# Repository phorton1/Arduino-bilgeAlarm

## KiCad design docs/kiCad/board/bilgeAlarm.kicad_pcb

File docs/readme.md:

# bilgeAlarm - Home

**Home** --
**[History](history.md)** --
**[Previous](previous.md)** --
**[Design](design.md)** --
**[Hardware](hardware.md)** --
**[Software](software.md)** --
**[UI](user_interface.md)**

The **bilgeAlarm** is the most important device I have created for my boat,
[**Rhapsody**](http://www.phorton.com/html/Rhapsody.html). It is a device
for monitoring the bilge pump(s) on the boat, sounding a **loud alarm**
if the bilge pump runs too long, or too often.  It is the result of
[almost sinking Rhapsody](history.md) one time when the bilge pump ran,
but could not be heard, until it **burnt out** and the boat took on 1000's of
gallons of water, resulting in **serious damage** and a huge amount of repairs ...
and time and money ... to fix the problems caused by the flooding.

This bilgeAlarm uses an **ESP32** and is based on an
[earlier](previous.md) **Arduino** project, now lost to antiquity,
that I called the *bilgePumpSwitch*.
It uses the [**myIOT**](https://github.com/phorton1/Arduino-libraries-myIOT) library
for parametrization and to allow me to control and monitor it remotely.
It has an **SD Card** to keep prodigious amounts of history about the bilge pump,
and uses **WS3812b** leds for visual indicators, and a **very loud car alarm**,
that can be heard above the motor running and the sound of the boat when she is
underway and crashing through waves to ensure that **I know** if there is a problem
with water entering the boat.

On these pages I will document the [**design**](design.md) of the bilgeAlarm along with
how I created the [**hardware**](hardware.md) and [**software**](software.md) for
the device and provide a rudimentary [**user guide**](user_interface.md) for using it.

All of the **source code, schematics,** and **files** needed to create this
device can be found within the **docs** folder:

- **kicad** - the kicad *schematics* and *pcb* layouts and the **flatcam** project and gcode files to mill and create the PCBs
- **fusion** - the fusion 360 design files for the plastic box
- **stl** - the STL files that I used for 3D printing the box
- **prusa** - the Prusa slicer files and resultant gcode I used to print the box

## Required Libraries

To build this project, you will need to install the
[**myIOT library**](https://github.com/phorton1/Arduino-libraries-myIOT)
and it's dependencies.  Please see that project for details about **installation**
and building.

In addition, this project makes use of two standard libraries that can
be installed to the **Arduino IDE** using the *Tools - Library Manager*:

- Adafruit_neoPixels
- LiquidCrystal_I2C

## License

This program is free software: you can redistribute it and/or modify
it under the terms of the GNU General Public License Version 3 as published by
the Free Software Foundation.

This program is distributed in the hope that it will be useful,
but WITHOUT ANY WARRANTY; without even the implied warranty of
MERCHANTABILITY or FITNESS FOR A PARTICULAR PURPOSE.  See the
GNU General Public License for more details.

Please see [LICENSE.TXT](https://github.com/phorton1/Arduino-libraries-myIOT/blob/master/LICENSE.TXT) for more information.

Next: The **[story](history.md)** behind the bilgeAlarm ...

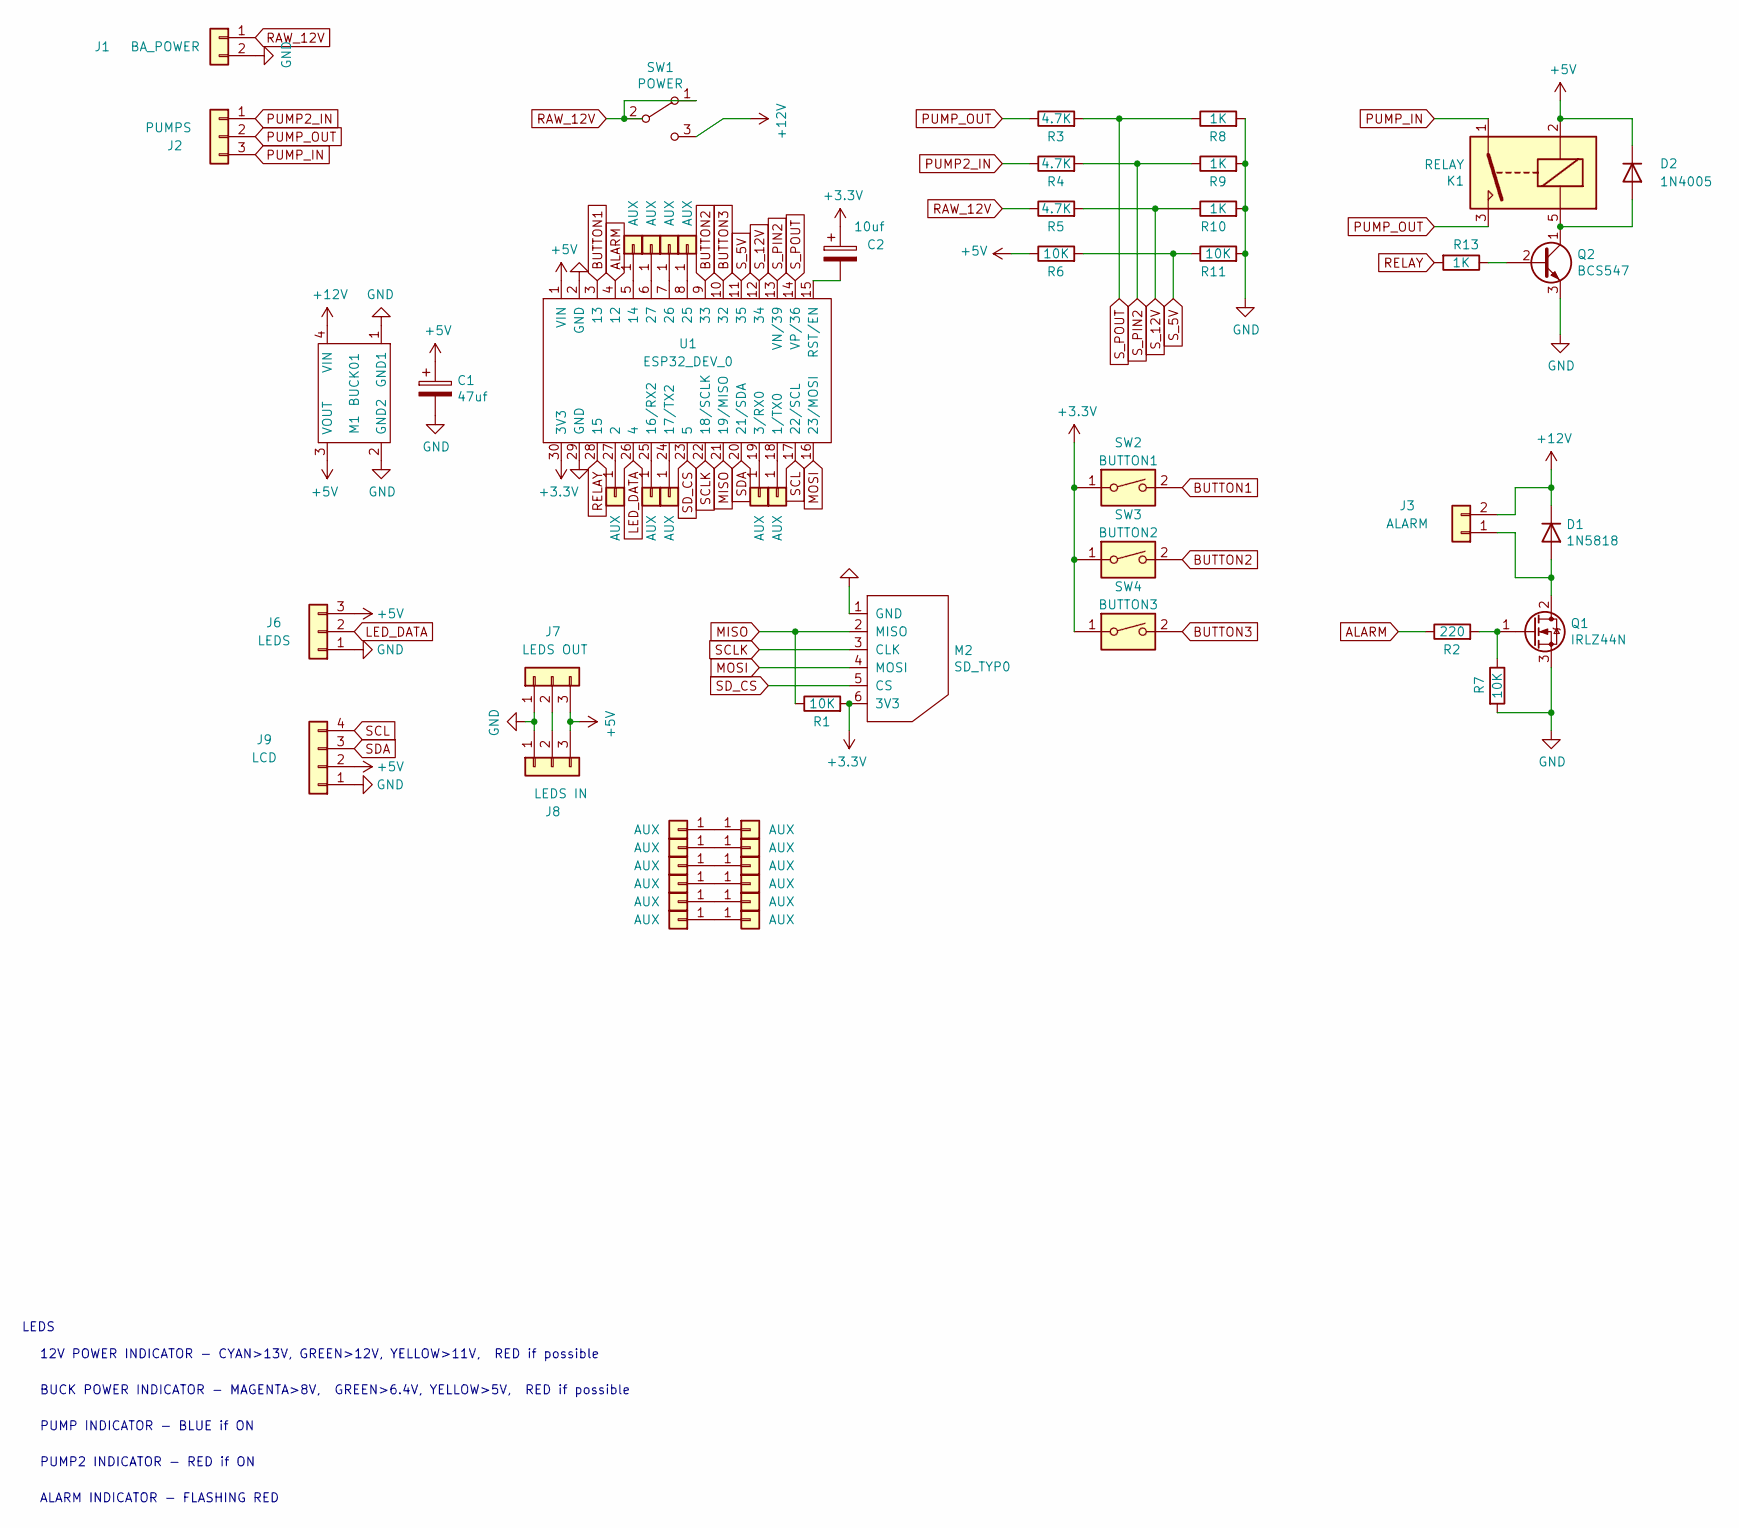
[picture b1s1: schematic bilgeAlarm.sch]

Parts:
C1: 47uf; CP_my100uf
C2: 10uf; CP_my10uf
D1: 1N5818; myDiodeSchotsky
D2: 1N4005; myDiodeSchotsky
J1: BA_POWER; myTerminalBlock_5.08x02
J2: PUMPS; myTerminalBlock_5.08x03
J3: ALARM; myTerminalBlock_5.08x02
J6: LEDS; myPinSocket_1x03
J7: LEDS OUT; myPinSocket_1x03
J8: LEDS IN; myPinSocket_1x03
J9: LCD; myPinSocket_1x04
J21, J22, J23, J24, J25, J26, J27, J28, J29, J30, J31, J32, J33, J34, J35, J36, J37, J38, J39, J40, J41: AUX; my1pin
K1: RELAY; myRelay
M1: BUCK01; myMini360BuckConverter
M2: SD_TYP0; SDCardReader
Q1: IRLZ44N; myTO-220-3
Q2: BCS547; my3pin
R1, R6, R7, R11: 10K; myResistor
R2: 220; myResistor
R3, R4, R5: 4.7K; myResistor
R8, R9, R10, R13: 1K; myResistor
SW1: POWER; mySwitchToggleSPDT
SW2: BUTTON1; myButton
SW3: BUTTON2; myButton
SW4: BUTTON3; myButton
U1: ESP32_DEV_0; myESP32DEV0

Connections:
+3V3: C2.1, M2.6 (3V3), R1.2, SW2.1, SW3.1, SW4.1, U1.30 (3V3)
+5V: C1.1, D2.1 (K), J6.3, J7.3, J8.3, J9.2, K1.2, M1.3 (VOUT), R6.1, U1.1 (VIN)
+12V: D1.1 (K), J3.2, M1.4 (VIN), SW1.3 (C)
ALARM: R2.1, U1.4 (12)
BUTTON1: SW2.2, U1.3 (13)
BUTTON2: SW3.2, U1.9 (33)
BUTTON3: SW4.2, U1.10 (32)
GND: C1.2, J1.2, J6.1, J7.1, J8.1, J9.1, M1.1 (GND1), M1.2 (GND2), M2.1 (GND), Q1.3 (S), Q2.3 (E), R7.2, R8.2, R9.2, R10.2, R11.2, U1.2 (GND), U1.29 (GND)
LED_DATA: J6.2, U1.26 (4)
MISO: M2.2 (MISO), R1.1, U1.21 (19/MISO)
MOSI: M2.4 (MOSI), U1.16 (23/MOSI)
unnamed: C2.2, U1.15 (RST/EN)
unnamed: D1.2 (A), J3.1, Q1.2 (D)
unnamed: D2.2 (A), K1.5, Q2.1 (C)
unnamed: J7.2, J8.2
unnamed: J21.1, U1.27 (2)
unnamed: J22.1, U1.25 (16/RX2)
unnamed: J23.1, U1.24 (17/TX2)
unnamed: J24.1, U1.5 (14)
unnamed: J25.1, U1.7 (26)
unnamed: J26.1, U1.8 (25)
unnamed: J27.1, U1.19 (3/RX0)
unnamed: J28.1, U1.18 (1/TX0)
unnamed: J29.1, U1.6 (27)
unnamed: J30.1, J36.1
unnamed: J31.1, J37.1
unnamed: J32.1, J38.1
unnamed: J33.1, J39.1
unnamed: J34.1, J40.1
unnamed: J35.1, J41.1
unnamed: Q1.1 (G), R2.2, R7.1
unnamed: Q2.2 (B), R13.1
PUMP2_IN: J2.1, R4.1
PUMP_IN: J2.3, K1.1
PUMP_OUT: J2.2, K1.3, R3.1
RAW_12V: J1.1, R5.1, SW1.1 (A), SW1.2 (B)
RELAY: R13.2, U1.28 (15)
SCL: J9.4, U1.17 (22/SCL)
SCLK: M2.3 (CLK), U1.22 (18/SCLK)
SDA: J9.3, U1.20 (21/SDA)
SD_CS: M2.5 (CS), U1.23 (5)
S_5V: R6.2, R11.1, U1.11 (35)
S_12V: R5.2, R10.1, U1.12 (34)
S_PIN2: R4.2, R9.1, U1.13 (VN/39)
S_POUT: R3.2, R8.1, U1.14 (VP/36)

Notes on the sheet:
LEDS
12V POWER INDICATOR - CYAN>13V, GREEN>12V, YELLOW>11V, RED if possible
BUCK POWER INDICATOR - MAGENTA>8V, GREEN>6.4V, YELLOW>5V, RED if possible
PUMP INDICATOR - BLUE if ON
PUMP2 INDICATOR - RED if ON
ALARM INDICATOR - FLASHING RED

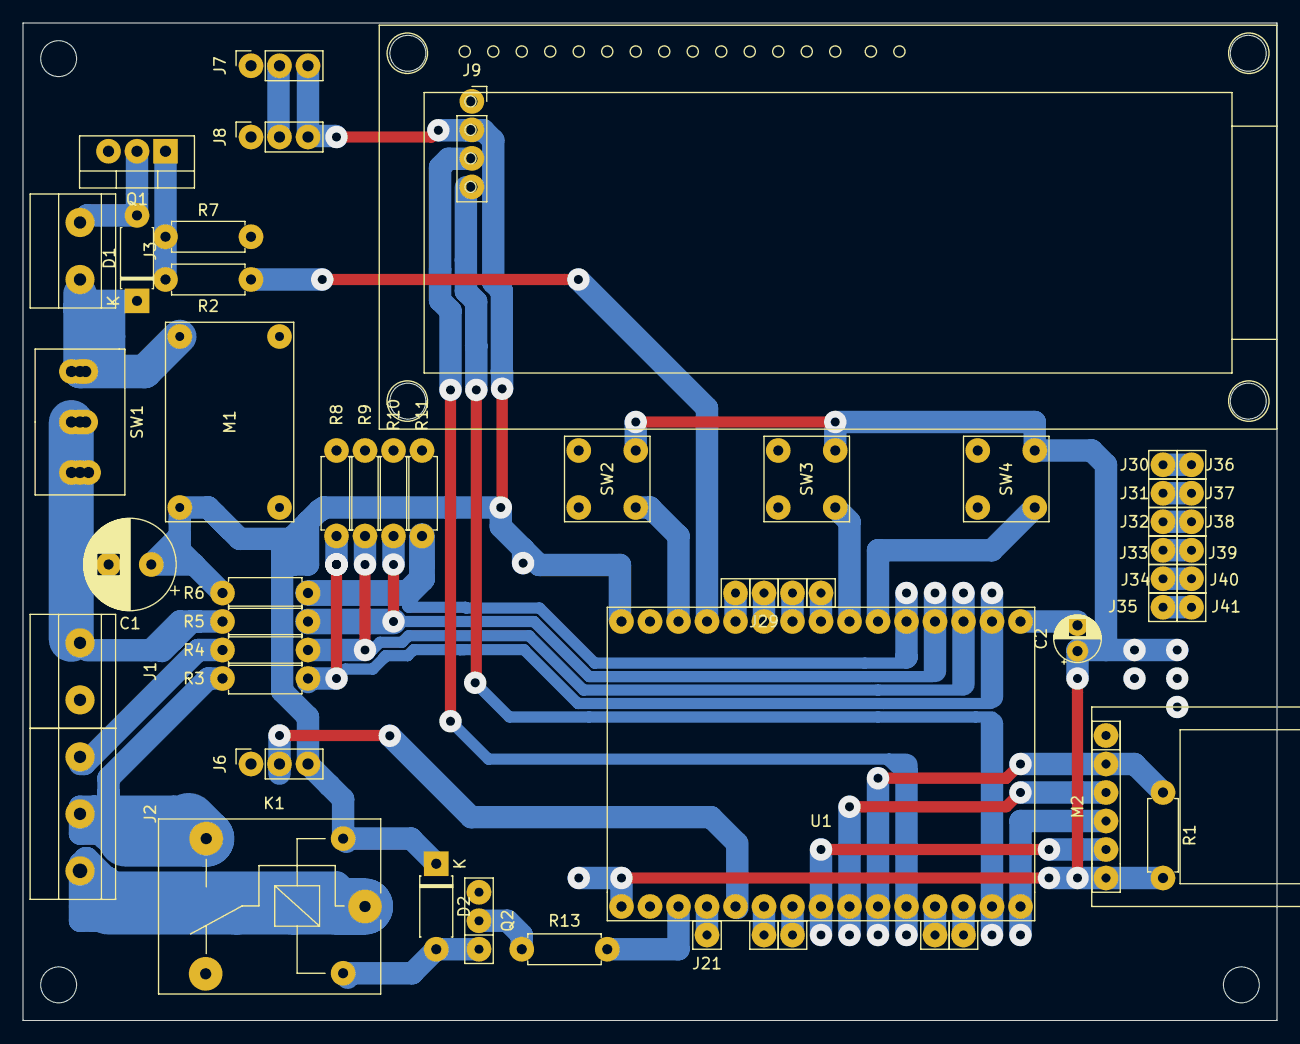
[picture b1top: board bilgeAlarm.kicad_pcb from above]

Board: 2 copper layers, 111.8 x 88.9 mm, 54 parts (0 on the bottom side), 45 nets.

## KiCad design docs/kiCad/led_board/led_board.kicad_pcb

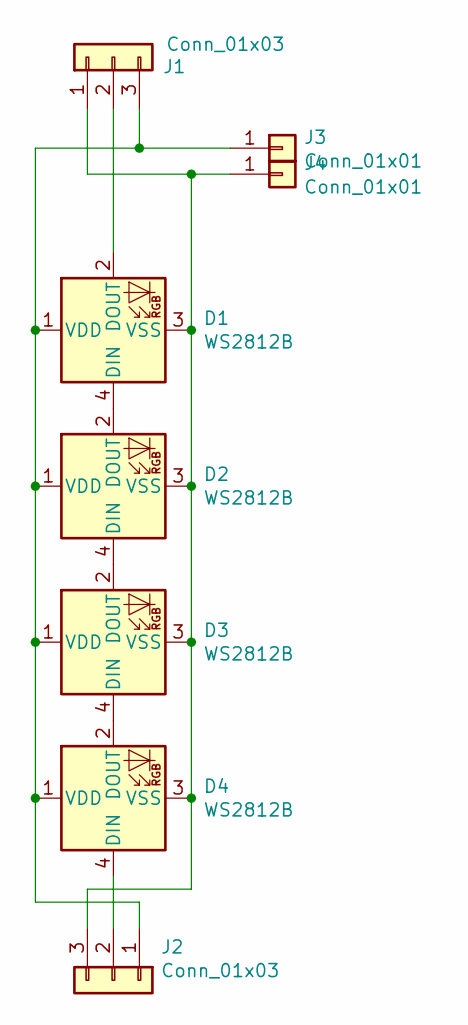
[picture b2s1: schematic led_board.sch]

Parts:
D1, D2, D3, D4: WS2812B; myWS2812
J1, J2: Conn_01x03; my3pin
J3, J4: Conn_01x01; my1pin

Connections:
unnamed: D1.1 (VDD), D2.1 (VDD), D3.1 (VDD), D4.1 (VDD), J1.3, J2.1, J3.1
unnamed: D1.2 (DOUT), J1.2
unnamed: D1.3 (VSS), D2.3 (VSS), D3.3 (VSS), D4.3 (VSS), J1.1, J2.3, J4.1
unnamed: D1.4 (DIN), D2.2 (DOUT)
unnamed: D2.4 (DIN), D3.2 (DOUT)
unnamed: D3.4 (DIN), D4.2 (DOUT)
unnamed: D4.4 (DIN), J2.2

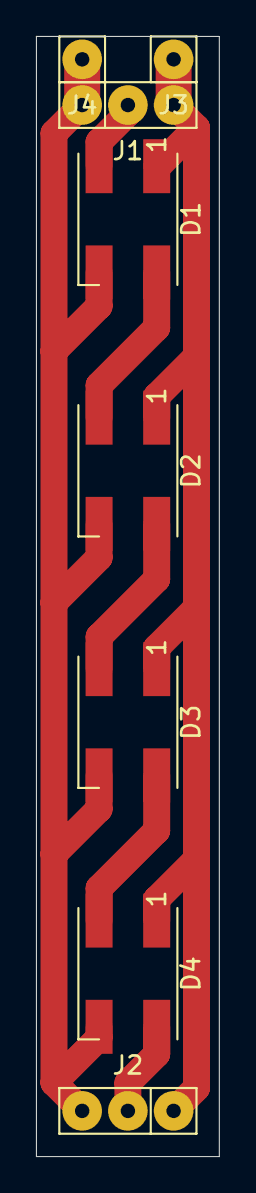
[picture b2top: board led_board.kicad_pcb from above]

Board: 2 copper layers, 10.2 x 62.2 mm, 8 parts (0 on the bottom side), 7 nets.

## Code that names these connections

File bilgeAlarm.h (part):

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#define PIN_ONBOARD_LED     2
#define PIN_OTHER_LED       33      // for old test ui - not on actual bilgeAlarm board

// PIN_SD_CS = 5
// PIN_MOSI  = 23
// PIN_SCLK  = 18
// PIN_MISO  = 19

#define PIN_BUTTON0         13
#define PIN_BUTTON1         33
#define PIN_BUTTON2         32

#define PIN_PUMP1_ON        36
#define PIN_PUMP2_ON        39
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// PIN_SDA = 21
// PIN_SCL = 22

#define PIN_RELAY           15
#define PIN_ALARM           12
#define PIN_LED_DATA        4


//------------------------
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// commands

#define ID_SELFTEST         "SELF_TEST"             // user command to run self test
#define ID_FORCE_RELAY      "FORCE_RELAY"           // the user command (switch) to force the relay on or off
#define ID_SUPPRESS         "SUPPRESS_ALARM"        // the user command (button) to suppress the alarm sound
#define ID_CLEAR_ERROR      "CLEAR_ERROR"           // the user command (button) to clear the current error
#define ID_CLEAR_HISTORY    "CLEAR_HISTORY"         // the user command (button) to clear the run_history
    // There are a number of scenarios about handling ALARMS.
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// configuration

#define ID_DISABLED         "ALARMS"                // _disabled = enabled,disabled = LEDs still light, but no errors, extra runs, or other functionality will take place
#define ID_ERR_RUN_TIME     "ERR_RUN_TIME"          // off,secs - pump running this many seconds or more is an "error alarm"
#define ID_CRIT_RUN_TIME    "CRIT_RUN_TIME"         // off,secs - pump running this many seconds or more is a "critical error alarm"
#define ID_ERR_PER_HOUR     "ERR_PER_HOUR"          // off,num - pump running more than this many times per hour is an "error alarm"
#define ID_ERR_PER_DAY      "ERR_PER_DAY"           // off,secs - pump running more than this many times per day is an "error alarm"
#define ID_EXTRA_RUN_TIME   "EXTRA_RUN_TIME"        // off,secs - how long to turn on relay if pump goes on,
#define ID_EXTRA_RUN_MODE   "EXTRA_RUN_MODE"        // at_start, after_end - whether to turn on relay when pump turns on, or when it turns off
#define ID_EXTRA_RUN_DELAY  "EXTRA_RUN_DELAY"       // millis, if after_end, how long after pump goes off before we turn on relay (long debounce time)
    // The "duration" does not include any time while the relay is on.
#define ID_SENSE_MILLIS     "SENSE_MILLIS"          // millis - how often to check the pump input pins, 5 minimum 30 default
#define ID_PUMP_DEBOUNCE    "PUMP_DEBOUNCE"         // millis - how long after the pump switch changes before we read it again
#define ID_RELAY_DEBOUNCE   "RELAY_DEBOUNCE"        // millis - how long after the relay goes off before we read the pump switch again
    // We read the pump sensors every SENSOR_MILLIS milliseconds.
    // The PUMP_DEBOUNCE value is how long after it changes before we read it again (though we act upon it immediately)
    // The RELAY_DEBOUNCE time is how long after we turn the relay off before we check the pump switch again.
    //    The relay will energize the pump switch and due to inductance in the motor, the switch may appear on
    //    when it is not really on for some period of time as the motor spins down.
#define ID_SW_THRESHOLD     "SW_THRESHOLD"          // analogRead() threshold for pump switches - default==900, see logfile if this value needs to be changed
#define ID_RUN_EMERGENCY    "RUN_EMERGENCY"         // off,secs - how long to turn on the relay as long as the emergency switch turns on
    // This will run the main pump if the emergency pump turns on, and continue running it for N more seconds than the emergency pump
#define ID_LED_BRIGHT       "LED_BRIGHT"            // 0..255 main ws2812 LED brightness
#define ID_EXT_LED_BRIGHT   "EXT_LED_BRIGHT"        // 0..255 ext ws2812 LED brightness
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#define STATE_EMERGENCY            0x0001       // the emergency pump switch was turned on
#define STATE_PUMP1_ON             0x0002       // the regular pump switch is on
#define STATE_PUMP2_ON             0x0004       // the emergency pump switch is on
#define STATE_RELAY_ON             0x0008       // the relay is on

// relay on states

#define STATE_RELAY_FORCED         0x0010      // the relay was forced on or off by the user
#define STATE_RELAY_EMERGENCY      0x0020      // the relay is on due to the ID_RUN_EMERGENCY value
#define STATE_RELAY_EXTRA          0x0040      // the relay is on due to the ID_EXTRA_RUN_TIME value

#define RELAY_STATE_ANY            (STATE_RELAY_FORCED | STATE_RELAY_EMERGENCY | STATE_RELAY_EXTRA)

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
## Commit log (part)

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2021-11-09 servoTest, esp32Camera, begin new bilgeAlarm architecture
2021-11-10 added time to test program
2021-11-10 SSDP Experiments
2021-11-10 removed underscore from uuid
2021-11-18 IOT Captive WIP
2021-11-19 Captive Portal WIP - added preferences
2021-11-22 IOT move prefs, get rid of network list,
2021-11-23 added basic derived callbacks
2021-11-24 added myIOTLog.h and cpp (got rid of myDebug)
2021-11-25 initial Bootstrap WebUI with SPIFFS upload - PROBLEM WITH TOP BYTES OF FLASH using 'default' partition table - MODIFIED default.csv in /Users/Patrick/Adrduino/blah to NOT USE top 2K of FLASH
2021-11-25 cleanup API a bit; implement WebUI file upload progress dialog
2021-11-29 barely working webUI topic switch
2021-11-29 added keyboardTask, MQQTConnectTask, basicOTA, and broke my css and js out of data/index.html
2021-11-30 minor UI changes
2021-11-30 rudimentary WebUI ws re-open strategy; random LED changes
2021-11-30 factored myIOTServer into separate objects; beefed up webUI ws auto-connect; headway into broadcast versus individual ws messages
2021-12-01 start centralizing Element types
2021-12-02 prep for element re-implementation
2021-12-03 first element based system; webUI needs to use classes instead of ids!
2021-12-03 cleanup javascript; prep for data driven dashboard
2021-12-03 rudimentary data driven webUI dashboard
2021-12-04 added SD Card, memory in log messages, and git_ignore arduino/libraries/esp32_sqlite
2021-12-05 removed slashes from element names; added DEBUG_LEVEL, and some future prefs; did factory_reset
2021-12-07 rudimentary graph
2021-12-10 playing with power monitoring, OTA, and hiding passwords
2021-12-13 reworked 'elements' into 'values' with general cleanup
2021-12-13 a little more cleanup
2021-12-14 implemented Enumerated type values
2021-12-15 minor fixes to COMMANDS
2021-12-15 implement WITH_SD and WITH_DATABASE defines in prep for turning on WITH_MQTT
2021-12-15 turn on WITH_MQTT, remove retained topics from RPI
2021-12-16 implement explicit ordering of items on UI tabs
2021-12-16 minor cleanups
2021-12-17 implmented WITH_TELNET
2021-12-23 renamed from bilgeAlarm2
2021-12-23 add docs/kiCad
2021-12-24 generate flatcam gcode files
2021-12-24 added combined isolation cuts
2021-12-25 initial testing of router port forwarding
2021-12-25 implement initial bilgeAlarm state machine
2021-12-26 cosmetic source cleanup
2021-12-28 implemented piVPN on rPi, mas-o-menus
2021-12-28 reworked Websocket auto-reconnect strategy
2021-12-28 added WS task, ferreted out LCD multi-core problem, tested VPN stuff
2021-12-28 turned of LCD test in loop()
2021-12-30 added myIOTDevice::getDeviceType() and cleaned up SSDP Usage for Perl myIOTServer
2022-01-03 added testDevice, cleaned up Name/Version/UUID=MAC, hostName for Wifi/Router
2022-01-03 WIP - myIOTServer basic WS multiplexer
2022-01-07 BIG COMMIT - added device_list to iotServer UI (multiple devices); added REBOOT and ws_closed disabling UI; added miami server user myiot_user and SSH keys for port forwarding; added working rPi serv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
2022-01-09 implement bilgeAlarm counting errors - still need javascript
2022-01-10 bilgeAlarm time and time_since & javascript; added IP address to device; renamed dash/device/system UI to dash/config/device
2022-01-11 IOT - logfiles if SD Card - Flat SD Card UI - GET passthrough from myIOTServer
2022-01-11 create/update myIOTDevice/docs ToDo.txt
2022-01-11 Start iotLCD_UI - cleaned up obs files and enum API and uint32_t usages
2022-01-12 initial LCD ui - cleaned up count error clearing
2022-01-13 factored bilgeAlarm.cpp into baRuns and baAlarm, changed baScreen/baButton to uiScreen/uiButton, implemented emergency alarm also gets counts, fixed UI duration display
2022-01-13 added git_ignore for expermintal build directory
2022-01-13 trying new gitignore pattern dir/**
2022-01-13 minor cleanup
2022-01-13 made stateMachine() task, publish in loop(), reworked counter logic, added error flags to history
2022-01-14 reworked durations with regards to relay and started counts immediately
2022-01-14 give precedence to TOO_MANY_DAY in LCD_UI history display
2022-01-15 completed LCD DEVICE and CONFIG value UI & moved some docs around, got rid of build directory
2022-01-18 implemented bilgeAlarm ws2812b LEDS (which also caused reworking some of the state logic and logging)
2022-01-18 Checking in Persistent Memory WIP
2022-01-19 implemented persistant SD run_history.dat file to work in conjunction with the RTC memory
2022-01-20 minor final changes before printing bilgeAlarm PCB
2022-01-20 generate bilgeAlaram gcode
2022-01-21 implemented 2nd, regular HTTP Server (via preferences file setting port to 8080), which sort of allows me to at least hit the myIOTServer from the iPad, but it is turned off in the preferences file a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
2022-01-22 reworked bilgeAlarm gcode
2022-01-24 additional gcode files for ill-fated, but nearly completed PCB
2022-01-26 minor changes to bilgeAlarm PCB gcode
2022-01-29 use analogRead and pump switch thresholds to avert alarm cycling
2022-01-29 added SCREEN_WIFI and SW_THRESHOLD
2022-01-29 added 12V and 5V power monitoring - note that 12V is measuring MAIN power and NOT the PUMP1 IN like would make sense
2022-01-30 bilgeAlarm led_board v2
2022-01-31 finish LED_BOARD, rework pixels at statrtup
2022-02-03 built box, added SelfTest
2022-02-03 fix mod error in history since calculation
2022-02-05 cleanup startup LEDs and remove pump from selfTest (as it upsets actual pump statistics)
2022-02-05 implement starting TIME_LAST_RUN and DUR from history file
2022-02-08 minor change to method call
2022-03-12 added !!emergency_relay_on to count_this_run if statement to try to avoid spurious history entry after running emerrgency relay AND turned off emergency relay in my config AND changed _disabled to tr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
2022-09-12 prep for BOARD2 - create copy of kiCad docs
2022-11-27 updatd ioCommon.js to do floats with precision 3
2023-01-01 got rid of docs/kicad *board2* folder and renamed "board1" to "board"
2023-01-02 removed DEMO_MODE - built & uploaded bilgeAlarm
2023-01-07 initial WIP documentation
2023-01-08 NO CHANGES - added a system schematic and turned on PCB layers to view
2023-01-08 WIP - documentation - is forcing review of LCD/button UIs
2023-01-15 kicad - commit reworked PCB board using my new symbols and 3d footprints
2023-01-15 added 3D printing/drawing files
2023-01-16 updated lightburn cover art
2023-01-16 clarified ui modes && button semantics
2023-04-17 removed VALUE_STYLE_NO_LOG from ID_POWER_12V
2023-05-27 added AUTO_REBOOT and upto 10 retries to INIT_SD_EARLY
2023-06-07 rebuilt with new captive.html
2023-07-05 updated to myIOT with ToolTips and PARAMS command
2023-07-05 changed Screen Debugging to VERBOSE
2023-07-08 added ID_DEVICE_URL (link to github device repository) to SSDP and WebUI
2024-03-01 moving /data directory to submodule of myIOT/data_master
2024-03-01 made 'data' directory into submodule of myIOT/data_master
2024-03-19 turn of PUMP1_ON state when turning off RELAY_ON to prevent endless loops of DELAYED_RELAYS - also cleaned up the debugging a bit
2024-03-23 fix and DEBUG switch debounce_times
2024-07-18 submodule(data) auto_commit(3ef3db13) iotCommon.js - added app disable control functionality
2024-07-19 submodule(data) auto_commit(9478759f) addl iotCommon.js submodule changes for control and disabled_classses
2024-09-21 submodule(data) auto_commit(83767cf1) Added a Widget tab to the main myIOT webpage; added jqplot CSS and JS files; wrote iotPlot.js prototype of charting within a "widget" - see fridgeController chec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
2024-09-22 submodule(data) auto_commit(0465efe4) myIOT Widets II - introduce basic HTTP caching; refactor myIOT iotPlot.js into iotCommon.js, cleanup Widget concepts and code; sanity checkcin
2024-09-22 submodule(data) auto_commit(e76456cf) iotPlot.js - minor change to Fix Zooming; otherwise "comments only"
2024-09-25 submodule(data) auto_commit(331f60b7) refined myIOT plotter with LEGENDS and using device specific PLOT_TYPES if available; theClock3 implementation of PLOT_CYCLES and PLOT_WAVES
2024-09-25 submodule(data) auto_commit(18ec6f60) iotPlot.js - missing ctx.lineWidth = 1; for plot itself
2024-09-26 submodule(data) auto_commit(68039dc2) prep for bilgeAlarm bar chart widget - reworked myIOTDataLog to send records from back of file until dt stamp is met, which required myIOTWebServer to use HTTP 1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
2024-09-29 added prototype bilgeAlarm jqPlot Widget using added "alt_data_format" and custom chart_header and chart_data code in onCustomLink(). modified myIOT/data index.html, iotChart.js, and iotCommon.js
2024-09-29 submodule(data) auto_commit(416ed000) added prototype bilgeAlarm jqPlot Widget using added "alt_data_format" and custom chart_header and chart_data code in onCustomLink(). modified myIOT/data index.h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
2024-10-01 submodule(data) auto_commit(2407a228) added global DEGREE_TYPE and VALUE_STYLE_TEMPERATURE, supprted in webUI, dataLog, and Charts
2024-10-06 submodule(data) auto_commit(28556b88) iotCommon.js - changed keep_alive timings and const's to vars to allow debugging at runtime
2024-10-10 submodule(data) auto_commit(b622c3ba) Use regular javascript alert instead of myAlert and hide progress on upload_error
2024-10-14 change bilgeAlarm to use void initSDCard()
2024-10-18 final debugging only changes before installing new dataLog version on boat
2024-10-21 submodule(data) auto_commit(b811e3f8) move generic uiButtons to myIOTButtons; implement initial tempController uiScreen and PCB board(s)
2024-10-25 submodule(data) auto_commit(fdbad871) fix myIOTServer with new chart stuff (pass uuids, caching, etc)
2025-12-15 submodule(data) auto_commit(b649fc3a) iotChart.js - added scheme for setting device specific series colors
2025-12-17 myIOT cleanup - got rid of Widget implementations
2025-12-18 submodule(data) auto_commit(b6ac0c88) starting in Arduino-boat-arirco, major rework of iotChart.js and how charts are implemented - use common chart.html instead of specific/extra_data/device_chart.h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
2025-12-18 submodule(data) auto_commit(1efc7b72) rework iotChart.js::determineNumberTicks() starting with drain_pump
2025-12-18 submodule(data) auto_commit(78894e93) change onChartResize() to use create_chart() instead of built in jqplot.replot()
2025-12-18 submodule(data) auto_commit(b923e44d) back to static html for chart.html; got rid of myIOTDataLog::getChartHtml() starting with tempController
2025-12-18 submodule(data) auto_commit(a4e2ed81) change chart.html and iotChart.js to use and remove style "degree_hidden" for devices that chart things with degrees
2025-12-18 submodule(data) auto_commit(a9754dbc) fixed renamed control _degree_type
2025-12-19 submodule(data) auto_commit(1cb3d61a) add onChartResize() back to chart.html
2025-12-19 submodule(data) auto_commit(253976a9) more changes to iotChart.js starting with tempController so at least refresh works *well* if no zooming involved
2025-12-19 commit parents
2025-12-20 submodule(data) auto_commit(eccd1fcc) iotChart.js - added save/restore of series visibility and refactored code
2026-02-22 submodule(data) auto_commit(37a6a76c) added framework for chart.html to pass "data_name" to allow multiple charts per device; ALSO store most recent chart period in browser storage
2026-03-04 added smaller (UINT8, CENTIGRADE8, UINT8x10) iotDataLog LOG_TYPES and updated client ctors
2026-03-04 submodule(data) auto_commit(75bcbcb5) iotChart.js - added smaller (UINT8, CENTIGRADE8, UINT8x10) iotDataLog LOG_TYPES and updated client ctors
2026-03-04 submodule(data) auto_commit(d6f02205) added myIotTempSensor "raw" accessors & used to shrink fridgeController.dataLog file size; got rid of FAKE_COMPRESSOR
2026-03-04 remove old comment
2026-03-05 added "boat" to the myIOTDevice advertised SSDP device URL
2026-03-05 submodule(data) auto_commit(ecc76888) update myIOT data submodule readme.md to remove forward references to actual implmented device repos
2026-04-03 add gcode .gitignores to project docs 3dp folders
2026-04-04 submodule(data) auto_commit(a0279fca) New iotChart tooltips and dataLog record maintenance feature.
